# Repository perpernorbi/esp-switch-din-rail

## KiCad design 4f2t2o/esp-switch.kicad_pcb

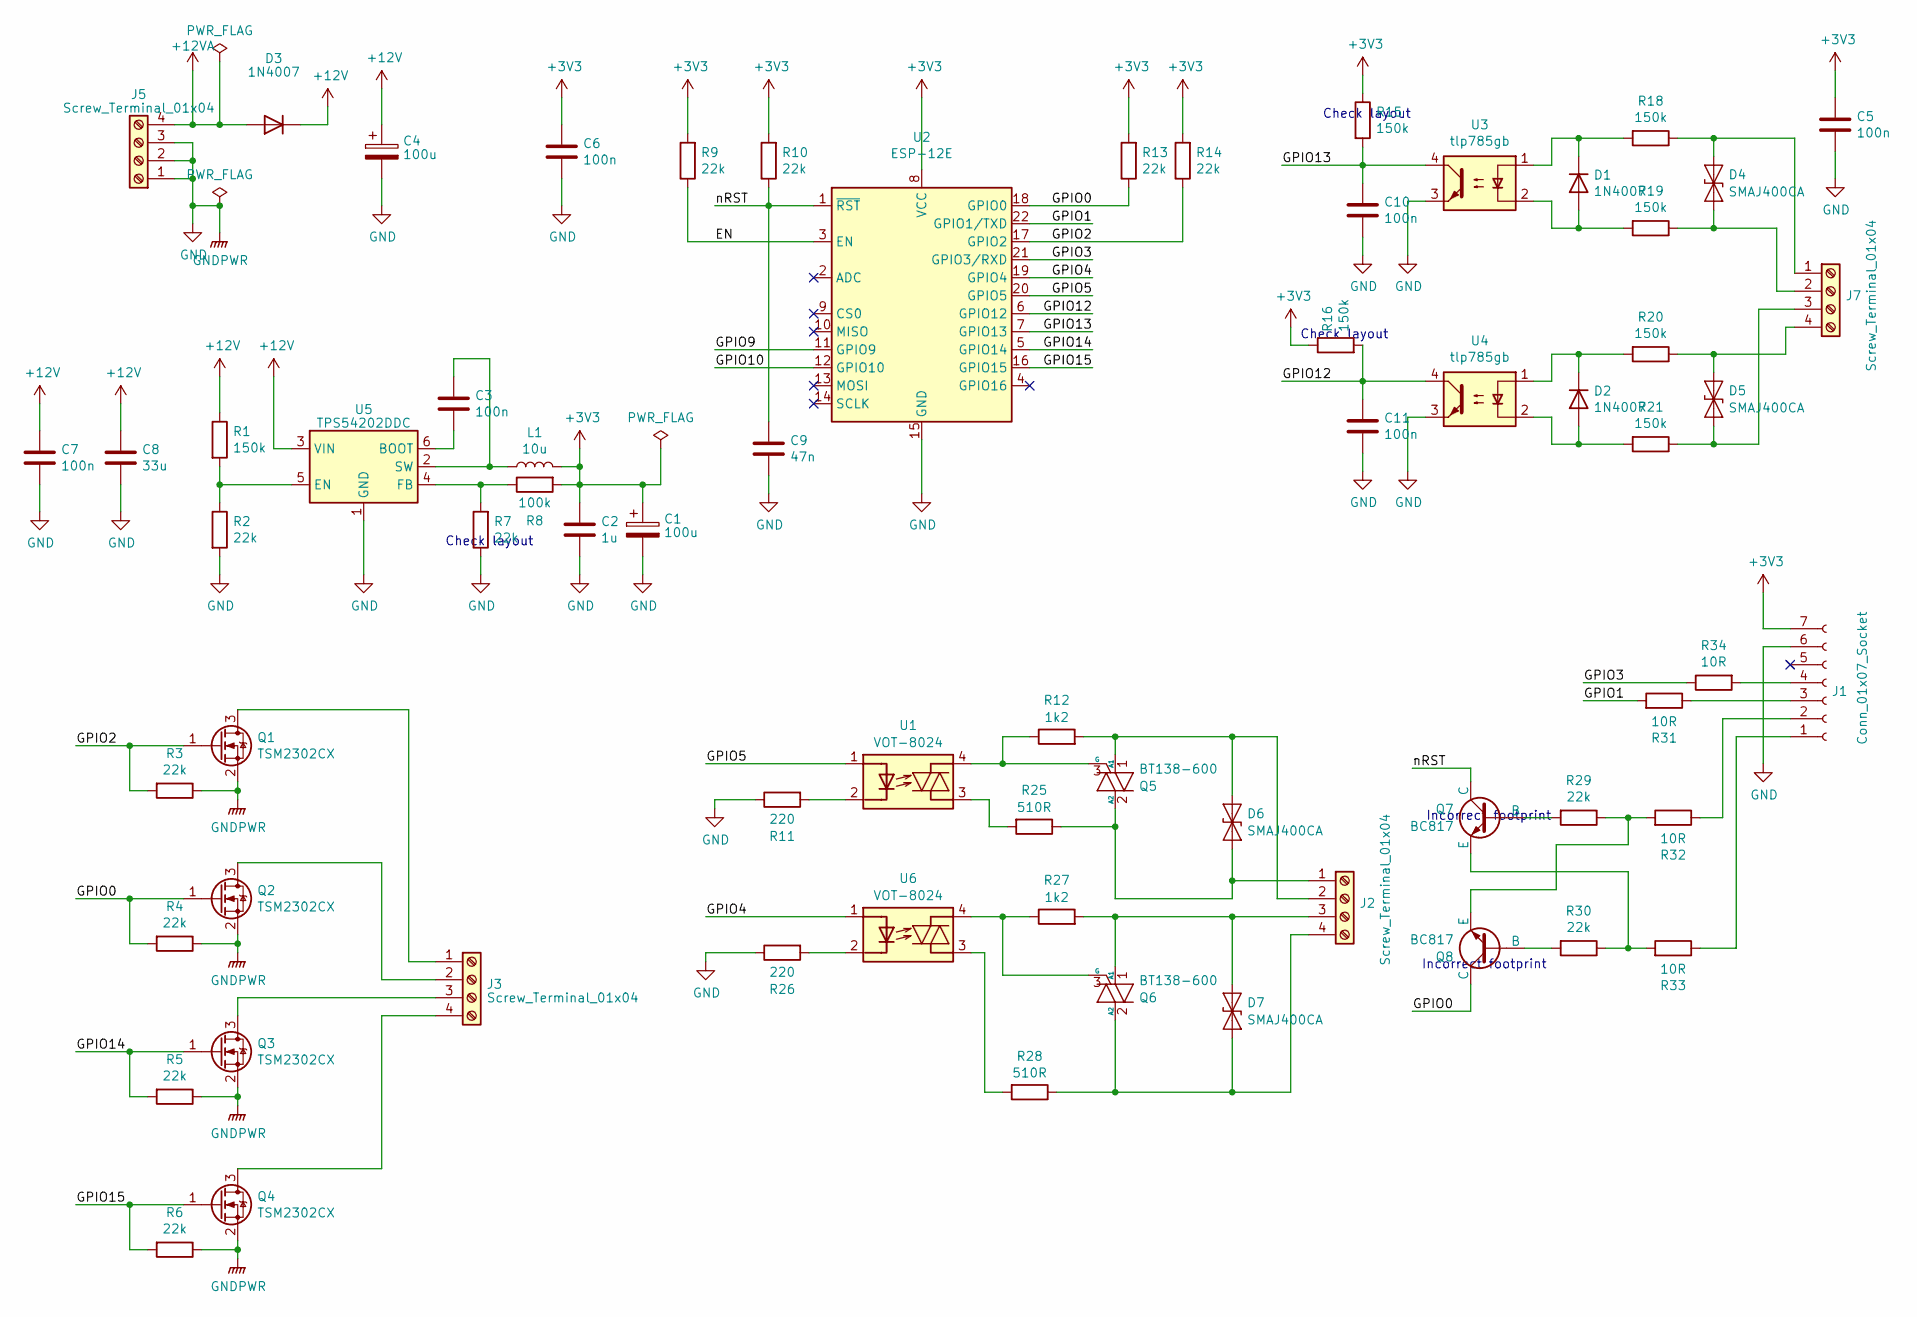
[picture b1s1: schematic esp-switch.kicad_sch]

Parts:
C1, C4: 100u; CP_Radial_D6.3mm_P2.50mm
C2: 1u; C_0805_2012Metric_Pad1.18x1.45mm_HandSolder
C3, C5, C6, C7, C10, C11: 100n; C_0805_2012Metric_Pad1.18x1.45mm_HandSolder
C8: 33u; C_1812_4532Metric_Pad1.57x3.40mm_HandSolder
C9: 47n; C_0805_2012Metric_Pad1.18x1.45mm_HandSolder
D1, D2: 1N4007; D_DO-15_P3.81mm_Vertical_AnodeUp
D3: 1N4007; D_DO-41_SOD81_P2.54mm_Vertical_KathodeUp
D4, D5, D6, D7: SMAJ400CA; D_SMA; Farnell 1827673
J1: Conn_01x07_Socket; PinSocket_1x07_P2.54mm_Horizontal
J2, J3: Screw_Terminal_01x04; ML-254-5-D-LCS
J5, J7: Screw_Terminal_01x04; ML-254-5-S-LCS
L1: 10u; L_6.5x6.5_H4.6
Q1, Q2, Q3, Q4: TSM2302CX; SOT-23_Handsoldering; Farnell 3121715
Q5, Q6: BT138-600; TO-252-2
Q7, Q8: BC817; SOT-23_Handsoldering
R1, R15, R16: 150k; R_0805_2012Metric_Pad1.20x1.40mm_HandSolder
R2, R3, R4, R5, R6, R7, R9, R10, R13, R14, R29, R30: 22k; R_0805_2012Metric_Pad1.20x1.40mm_HandSolder
R8: 100k; R_0805_2012Metric_Pad1.20x1.40mm_HandSolder
R11, R26: 220; R_0805_2012Metric_Pad1.20x1.40mm_HandSolder
R12, R27: 1k2; R_Axial_DIN0207_L6.3mm_D2.5mm_P2.54mm_Vertical
R18, R19, R20, R21: 150k; R_Axial_DIN0207_L6.3mm_D2.5mm_P2.54mm_Vertical
R25, R28: 510R; R_Axial_DIN0207_L6.3mm_D2.5mm_P2.54mm_Vertical
R31, R32, R33, R34: 10R; R_0805_2012Metric_Pad1.20x1.40mm_HandSolder
U1, U6: VOT-8024; DIP-4_W7.62mm_SMDSocket_SmallPads; Farnell 3778033
U2: ESP-12E
U3, U4: tlp785gb; DIP-4_W7.62mm
U5: TPS54202DDC; SOT-23-6_Handsoldering

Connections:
+3V3: C1.1, C2.1, C5.1, C6.1, J1.7, L1.1, R8.2, R9.2, R10.2, R13.2, R14.2, R15.1, R16.1, U2.8 (VCC)
+12V: C4.1, C7.1, C8.1, D3.1 (K), R1.1, U5.3 (VIN)
+12VA: D3.2 (A), J5.4
/EN: R9.1, U2.3 (EN)
/GPIO0: Q2.1 (G), Q8.1 (C), R4.2, R13.1, U2.18 (GPIO0)
/GPIO1: R31.2, U2.22 (GPIO1/TXD)
/GPIO2: Q1.1 (G), R3.2, R14.1, U2.17 (GPIO2)
/GPIO3: R34.1, U2.21 (GPIO3/RXD)
/GPIO4: U2.19 (GPIO4), U6.1 (A)
/GPIO5: U1.1 (A), U2.20 (GPIO5)
/GPIO9: U2.11 (GPIO9)
/GPIO10: U2.12 (GPIO10)
/GPIO12: C11.1, R16.2, U2.6 (GPIO12), U4.4
/GPIO13: C10.1, R15.2, U2.7 (GPIO13), U3.4
/GPIO14: Q3.1 (G), R5.2, U2.5 (GPIO14)
/GPIO15: Q4.1 (G), R6.2, U2.16 (GPIO15)
/nRST: C9.1, Q7.1 (C), R10.1, U2.1 (~RST)
GND: C1.2, C2.2, C4.2, C5.2, C6.2, C7.2, C8.2, C9.2, C10.2, C11.2, J1.6, J5.1, J5.2, J5.3, Q1.2 (S), Q2.2 (S), Q3.2 (S), Q4.2 (S), R2.2, R3.1, R4.1, R5.1, R6.1, R7.1, R11.1, R26.1, U2.15 (GND), U3.3, U4.3, U5.1 (GND)
unnamed: D1.2 (A), R19.2, U3.2
unnamed: D1.1 (K), R18.2, U3.1
unnamed: D2.2 (A), R21.2, U4.2
unnamed: D2.1 (K), R20.2, U4.1
unnamed: D4.1 (A1), J7.2, R19.1
unnamed: D4.2 (A2), J7.1, R18.1
unnamed: D5.1 (A1), J7.3, R21.1
unnamed: D5.2 (A2), J7.4, R20.1
unnamed: D6.1 (A1), J2.2, Q5.1 (A1), R12.2
unnamed: D6.2 (A2), J2.1, Q5.2 (A2), R25.1
unnamed: D7.1 (A1), J2.3, Q6.1 (A1), R27.2
unnamed: D7.2 (A2), J2.4, Q6.2 (A2), R28.1
unnamed: J1.1, R33.1
unnamed: J1.2, R32.1
unnamed: J1.3, R31.1
unnamed: J1.4, R34.2
unnamed: J3.1, Q1.3 (D)
unnamed: J3.2, Q2.3 (D)
unnamed: J3.3, Q3.3 (D)
unnamed: J3.4, Q4.3 (D)
unnamed: Q5.3 (G), R12.1, U1.4 (R)
unnamed: Q6.3 (G), R27.1, U6.4 (R)
unnamed: Q7.2 (B), R29.2
unnamed: Q7.3 (E), R30.1, R33.2
unnamed: Q8.2 (B), R30.2
unnamed: Q8.3 (E), R29.1, R32.2
unnamed: R25.2, U1.3 (R)
unnamed: R28.2, U6.3 (R)
unnamed: R11.2, U1.2 (K)
unnamed: C3.2, U5.6 (BOOT)
unnamed: R1.2, R2.1, U5.5 (EN)
unnamed: R7.2, R8.1, U5.4 (FB)
unnamed: C3.1, L1.2, U5.2 (SW)
unnamed: R26.2, U6.2 (K)

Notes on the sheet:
Incorrect footprint
Check layout

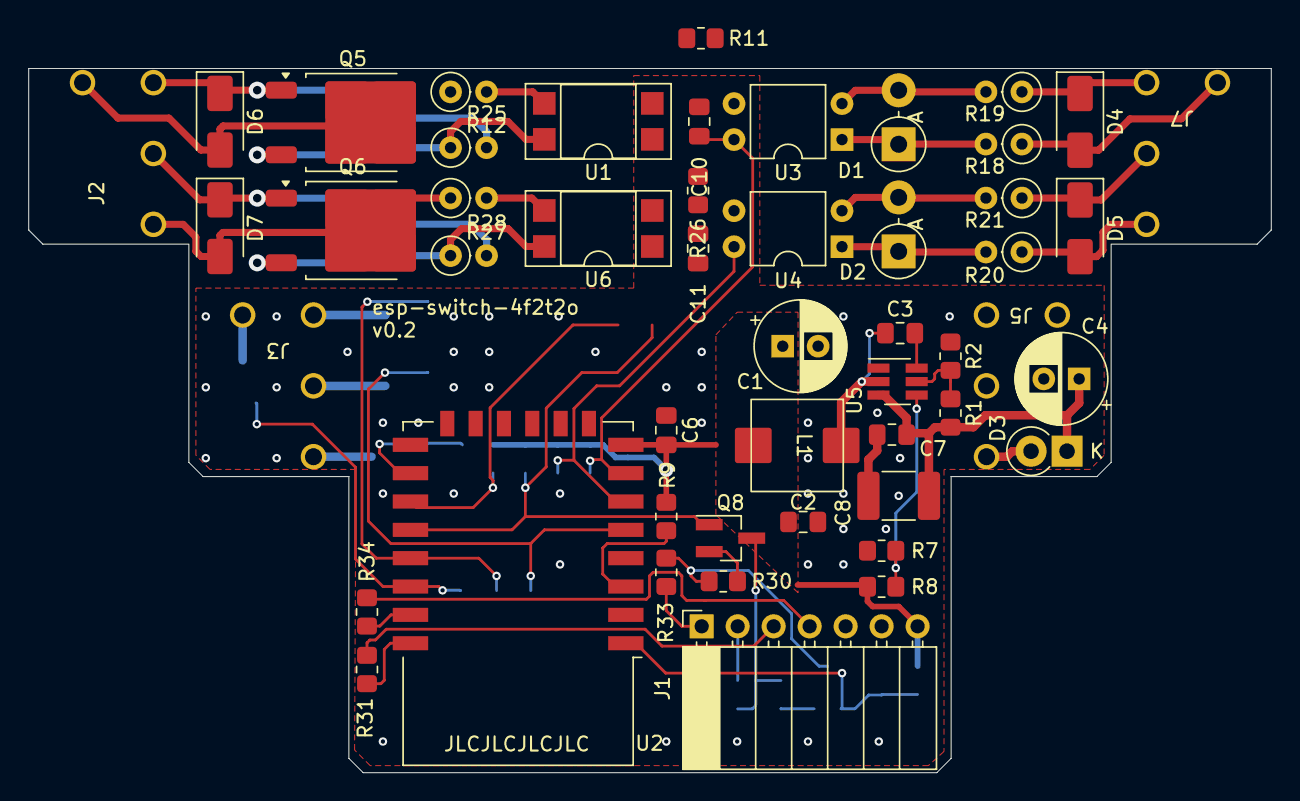
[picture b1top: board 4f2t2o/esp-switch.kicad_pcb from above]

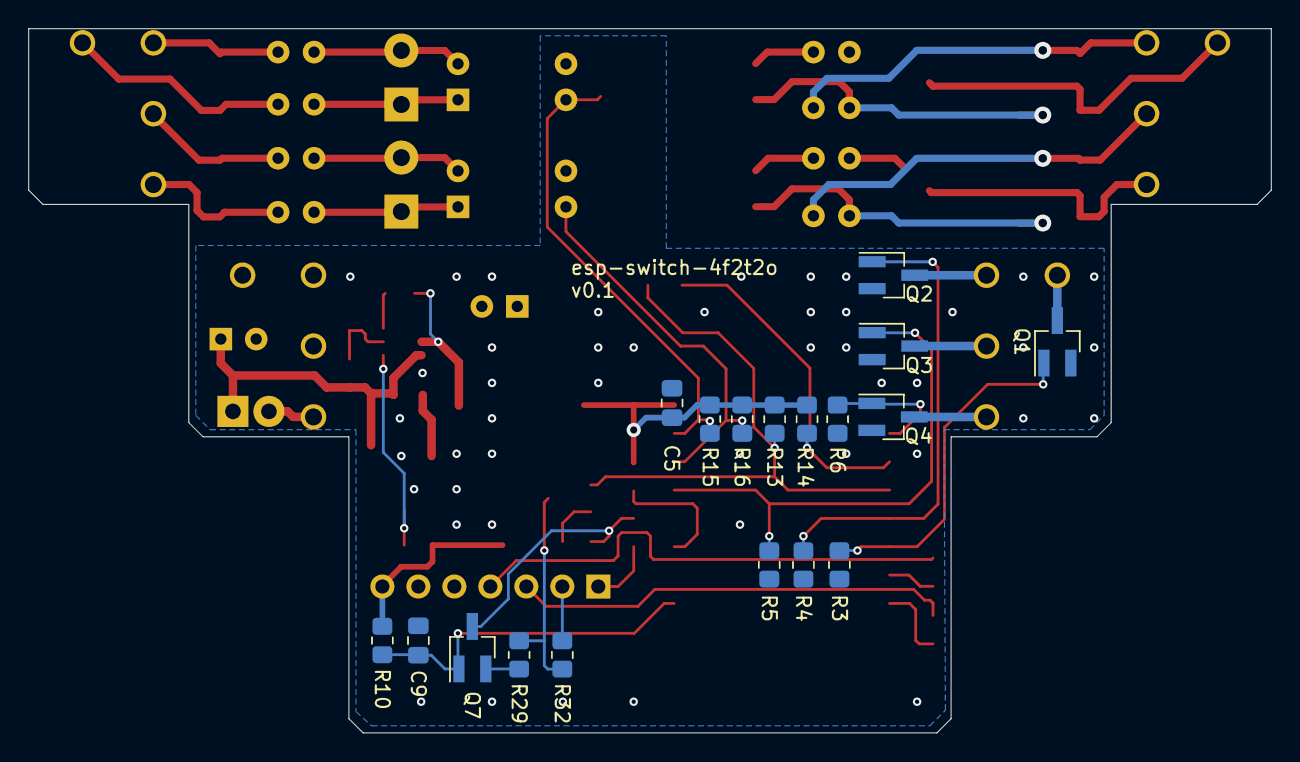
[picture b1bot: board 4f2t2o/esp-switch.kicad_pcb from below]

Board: 2 copper layers, 87.7 x 49.7 mm, 68 parts (18 on the bottom side), 50 nets.

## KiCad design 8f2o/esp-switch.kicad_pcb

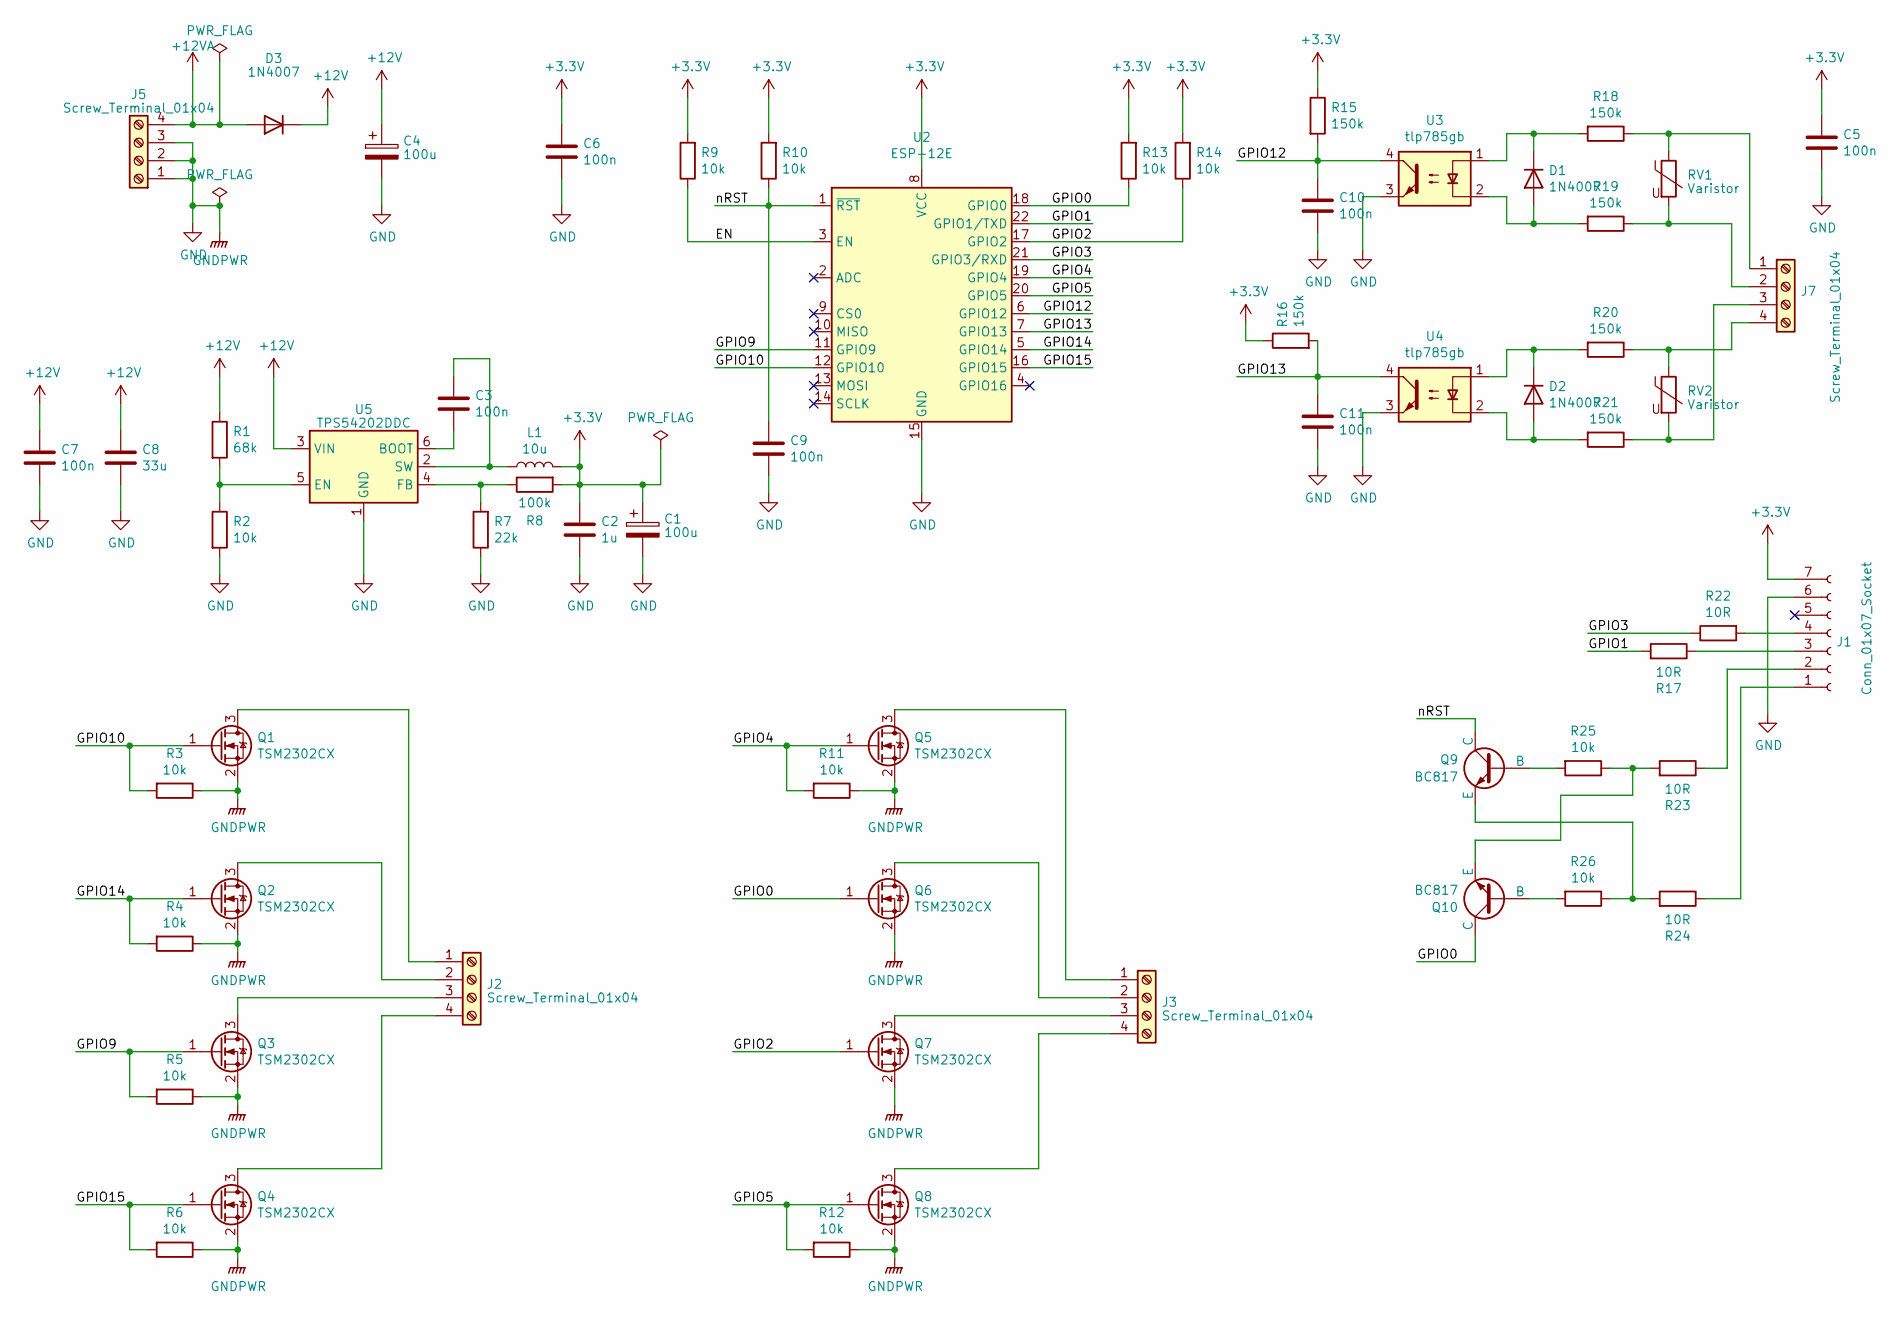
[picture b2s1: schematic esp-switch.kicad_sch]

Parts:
C1, C4: 100u; CP_Radial_D6.3mm_P2.50mm
C2: 1u; C_0805_2012Metric_Pad1.18x1.45mm_HandSolder
C3, C5, C6, C7, C9, C10, C11: 100n; C_0805_2012Metric_Pad1.18x1.45mm_HandSolder
C8: 33u; C_1812_4532Metric_Pad1.57x3.40mm_HandSolder
D1, D2: 1N4007; D_DO-15_P3.81mm_Vertical_AnodeUp
D3: 1N4007; D_DO-41_SOD81_P2.54mm_Vertical_KathodeUp
J1: Conn_01x07_Socket; PinSocket_1x07_P2.54mm_Horizontal
J2, J3: Screw_Terminal_01x04; ML-254-5-D-LCS
J5, J7: Screw_Terminal_01x04; ML-254-5-S-LCS
L1: 10u; L_6.5x6.5_H4.6
Q1, Q2, Q3, Q4, Q5, Q6, Q7, Q8: TSM2302CX; SOT-23_Handsoldering
Q9, Q10: BC817; SOT-23_Handsoldering
R1: 68k; R_0805_2012Metric_Pad1.20x1.40mm_HandSolder
R2, R3, R4, R5, R6, R9, R10, R11, R12, R13, R14, R25, R26: 10k; R_0805_2012Metric_Pad1.20x1.40mm_HandSolder
R7: 22k; R_0805_2012Metric_Pad1.20x1.40mm_HandSolder
R8: 100k; R_0805_2012Metric_Pad1.20x1.40mm_HandSolder
R15, R16: 150k; R_0805_2012Metric_Pad1.20x1.40mm_HandSolder
R17, R22, R23, R24: 10R; R_0805_2012Metric_Pad1.20x1.40mm_HandSolder
R18, R19, R20, R21: 150k; R_Axial_DIN0207_L6.3mm_D2.5mm_P10.16mm_Horizontal
RV1, RV2: Varistor; RV_Disc_D7mm_W5.7mm_P5mm
U2: ESP-12E
U3, U4: tlp785gb; DIP-4_W7.62mm
U5: TPS54202DDC; SOT-23-6_Handsoldering

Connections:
+3V3: C1.1, C2.1, C5.1, C6.1, J1.7, L1.1, R8.2, R9.2, R10.2, R13.2, R14.2, R15.1, R16.1, U2.8 (VCC)
+12V: C4.1, C7.1, C8.1, D3.1 (K), R1.1, U5.3 (VIN)
+12VA: D3.2 (A), J5.4
/EN: R9.1, U2.3 (EN)
/GPIO0: Q6.1 (G), Q10.1 (C), R13.1, U2.18 (GPIO0)
/GPIO1: R17.2, U2.22 (GPIO1/TXD)
/GPIO2: Q7.1 (G), R14.1, U2.17 (GPIO2)
/GPIO3: R22.1, U2.21 (GPIO3/RXD)
/GPIO4: Q5.1 (G), R11.2, U2.19 (GPIO4)
/GPIO5: Q8.1 (G), R12.2, U2.20 (GPIO5)
/GPIO9: Q3.1 (G), R5.2, U2.11 (GPIO9)
/GPIO10: Q1.1 (G), R3.2, U2.12 (GPIO10)
/GPIO12: C10.1, R15.2, U2.6 (GPIO12), U3.4
/GPIO13: C11.1, R16.2, U2.7 (GPIO13), U4.4
/GPIO14: Q2.1 (G), R4.2, U2.5 (GPIO14)
/GPIO15: Q4.1 (G), R6.2, U2.16 (GPIO15)
/nRST: C9.1, Q9.1 (C), R10.1, U2.1 (~RST)
GND: C1.2, C2.2, C4.2, C5.2, C6.2, C7.2, C8.2, C9.2, C10.2, C11.2, J1.6, J5.1, J5.2, J5.3, Q1.2 (S), Q2.2 (S), Q3.2 (S), Q4.2 (S), Q5.2 (S), Q6.2 (S), Q7.2 (S), Q8.2 (S), R2.2, R3.1, R4.1, R5.1, R6.1, R7.1, R11.1, R12.1, U2.15 (GND), U3.3, U4.3, U5.1 (GND)
unnamed: D1.2 (A), R19.2, U3.2
unnamed: D1.1 (K), R18.2, U3.1
unnamed: D2.2 (A), R21.2, U4.2
unnamed: D2.1 (K), R20.2, U4.1
unnamed: J1.1, R24.1
unnamed: J1.2, R23.1
unnamed: J1.3, R17.1
unnamed: J1.4, R22.2
unnamed: J2.1, Q1.3 (D)
unnamed: J2.2, Q2.3 (D)
unnamed: J2.3, Q3.3 (D)
unnamed: J2.4, Q4.3 (D)
unnamed: J3.1, Q5.3 (D)
unnamed: J3.2, Q6.3 (D)
unnamed: J3.3, Q7.3 (D)
unnamed: J3.4, Q8.3 (D)
unnamed: J7.1, R18.1, RV1.1
unnamed: J7.2, R19.1, RV1.2
unnamed: J7.3, R21.1, RV2.2
unnamed: J7.4, R20.1, RV2.1
unnamed: Q9.2 (B), R25.2
unnamed: Q9.3 (E), R24.2, R26.1
unnamed: Q10.2 (B), R26.2
unnamed: Q10.3 (E), R23.2, R25.1
unnamed: C3.2, U5.6 (BOOT)
unnamed: R1.2, R2.1, U5.5 (EN)
unnamed: R7.2, R8.1, U5.4 (FB)
unnamed: C3.1, L1.2, U5.2 (SW)

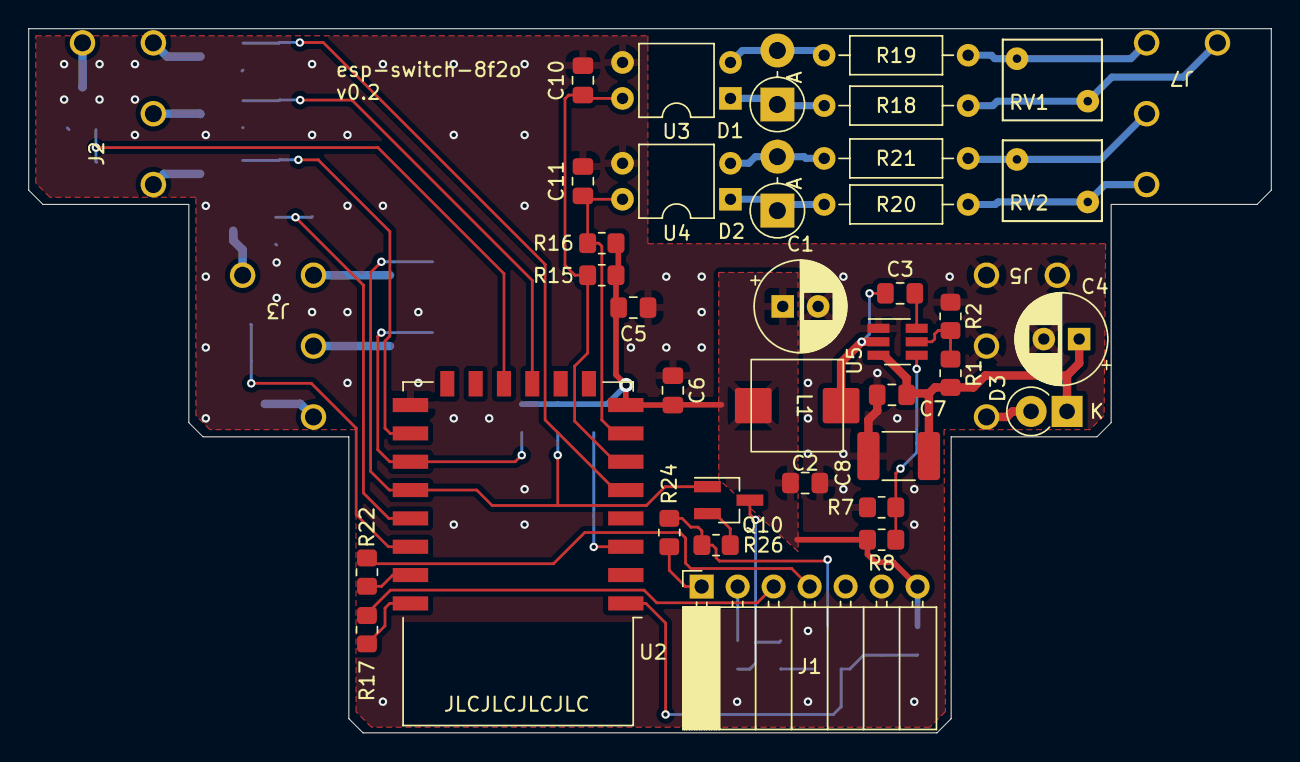
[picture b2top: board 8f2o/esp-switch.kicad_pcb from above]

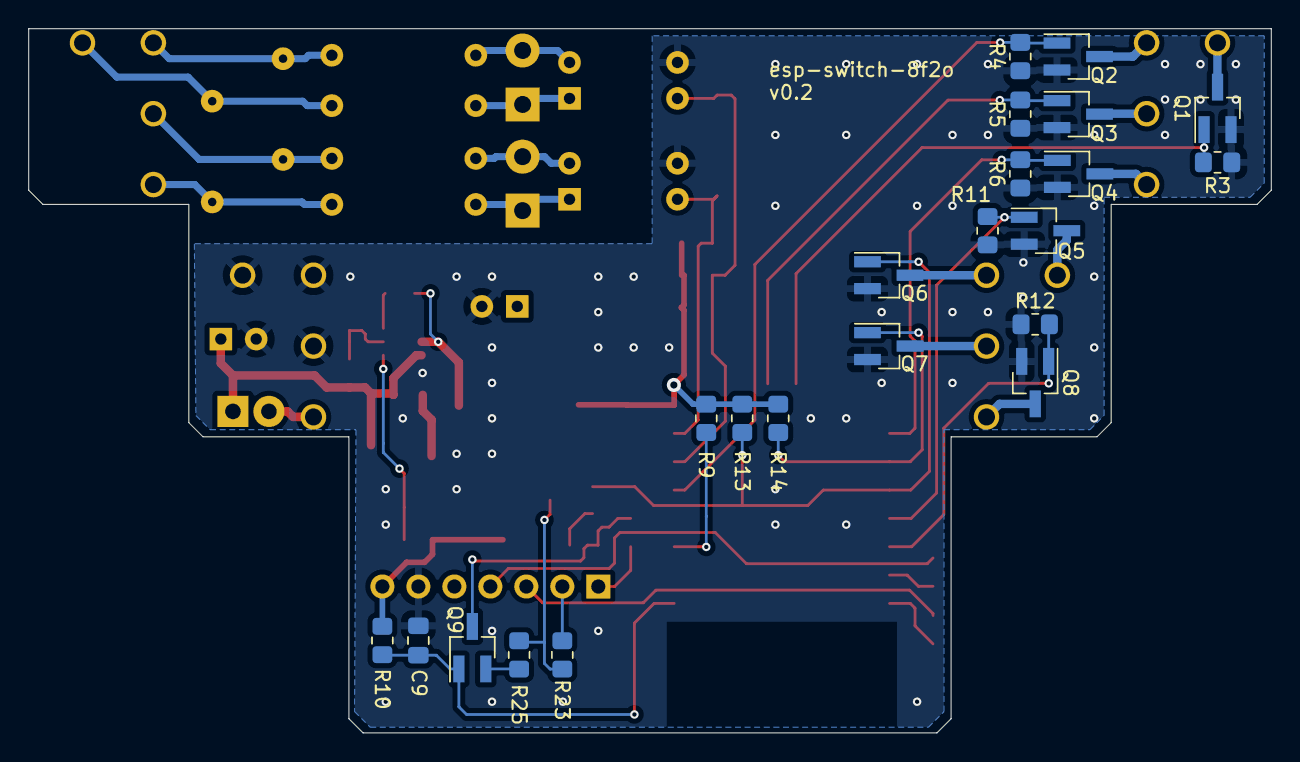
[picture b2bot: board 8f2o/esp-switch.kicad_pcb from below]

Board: 2 copper layers, 87.7 x 49.7 mm, 62 parts (22 on the bottom side), 46 nets.

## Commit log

2023-10-22 v0.1 for 8f2o and 4f2t2o
2023-10-22 Update values
2023-10-22 Add missing files
